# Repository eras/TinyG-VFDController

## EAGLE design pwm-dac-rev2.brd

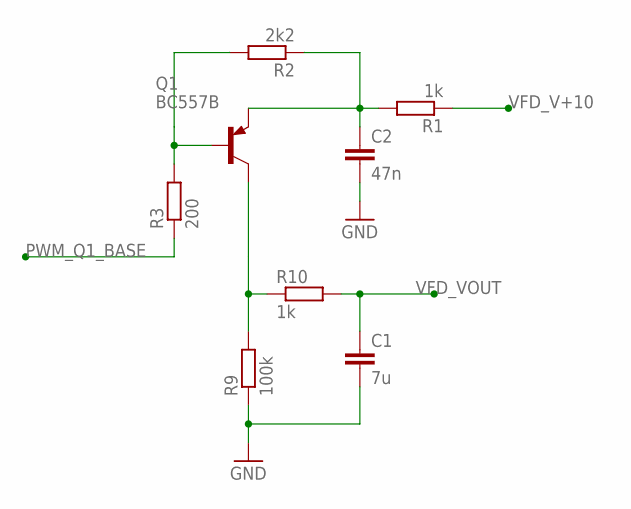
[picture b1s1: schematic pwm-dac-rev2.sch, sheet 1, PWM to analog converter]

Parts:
C1: 7u; C025-025X050
C2: 47n; C025-025X050
Q1: BC557B; TO92-EBC-OVAL
R1, R10: 1k; 0204/7
R2: 2k2; 0204/7
R3: 200; 0204/7
R9: 100k; 0204/7

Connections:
GND: C1.2, C2.2, R9.1; also elsewhere on the board
unnamed: C2.1, Q1.E, R1.2, R2.1
PWM_Q1_BASE: R3.1; also elsewhere on the board
Q3_B: Q1.B, R2.2, R3.2
Q3_C: Q1.C, R9.2, R10.1
VFD_V+10: R1.1; also elsewhere on the board
VFD_VOUT: C1.1, R10.2; also elsewhere on the board

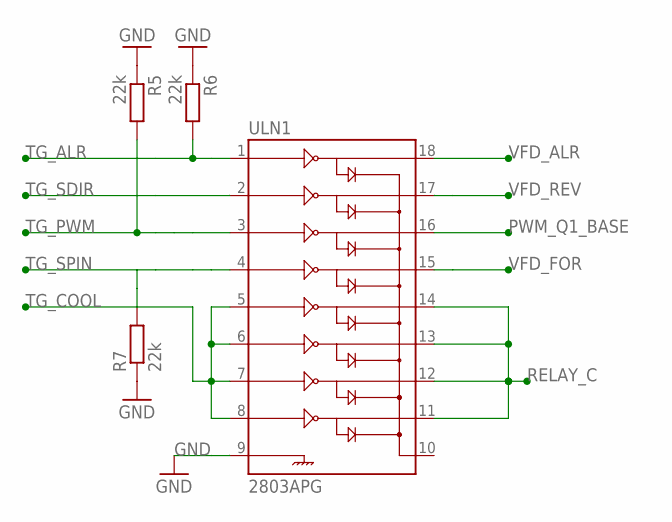
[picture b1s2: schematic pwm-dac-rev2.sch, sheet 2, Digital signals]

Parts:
R5, R6, R7: 22k; 0204/7
ULN1: 2803APG; DIL18

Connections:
GND: R5.1, R6.1, R7.1, ULN1.9; also elsewhere on the board
PWM_Q1_BASE: ULN1.16; also elsewhere on the board
RELAY_C: ULN1.11, ULN1.12, ULN1.13, ULN1.14; also elsewhere on the board
TG_ALR: R6.2, ULN1.1; also elsewhere on the board
TG_COOL: ULN1.5, ULN1.6, ULN1.7, ULN1.8; also elsewhere on the board
TG_PWM: R5.2, ULN1.3; also elsewhere on the board
TG_SDIR: ULN1.2; also elsewhere on the board
TG_SPIN: R7.2, ULN1.4; also elsewhere on the board
VFD_ALR: ULN1.18; also elsewhere on the board
VFD_FOR: ULN1.15; also elsewhere on the board
VFD_REV: ULN1.17; also elsewhere on the board

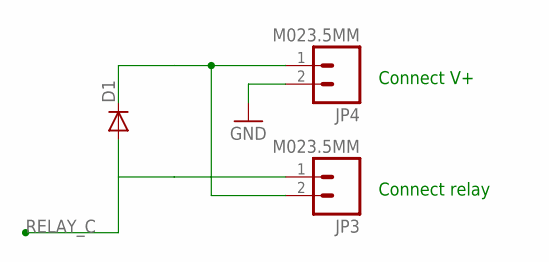
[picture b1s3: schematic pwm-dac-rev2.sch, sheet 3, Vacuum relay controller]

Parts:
D1: DIODE1N4148; DIODE-1N4148
JP3, JP4: M023.5MM; SCREWTERMINAL-3.5MM-2

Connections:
GND: JP4.2; also elsewhere on the board
unnamed: D1.C, JP3.2, JP4.1
RELAY_C: D1.A, JP3.1; also elsewhere on the board

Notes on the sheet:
Connect relay
Connect V+

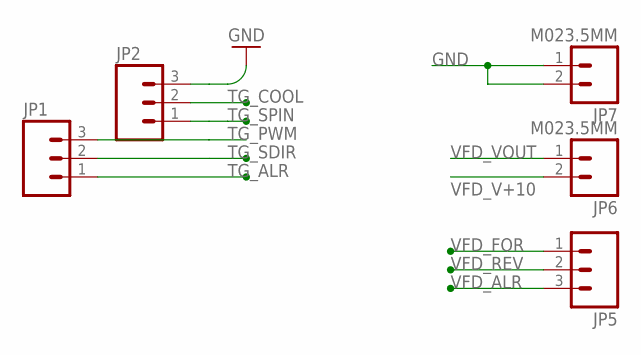
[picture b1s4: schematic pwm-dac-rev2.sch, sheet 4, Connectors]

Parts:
JP1, JP2, JP5: M03SCREW; SCREWTERMINAL-3.5MM-3
JP6, JP7: M023.5MM; SCREWTERMINAL-3.5MM-2

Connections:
GND: JP2.3, JP7.1, JP7.2; also elsewhere on the board
TG_ALR: JP1.1; also elsewhere on the board
TG_COOL: JP2.2; also elsewhere on the board
TG_PWM: JP1.3; also elsewhere on the board
TG_SDIR: JP1.2; also elsewhere on the board
TG_SPIN: JP2.1; also elsewhere on the board
VFD_ALR: JP5.3; also elsewhere on the board
VFD_FOR: JP5.1; also elsewhere on the board
VFD_REV: JP5.2; also elsewhere on the board
VFD_V+10: JP6.2; also elsewhere on the board
VFD_VOUT: JP6.1; also elsewhere on the board

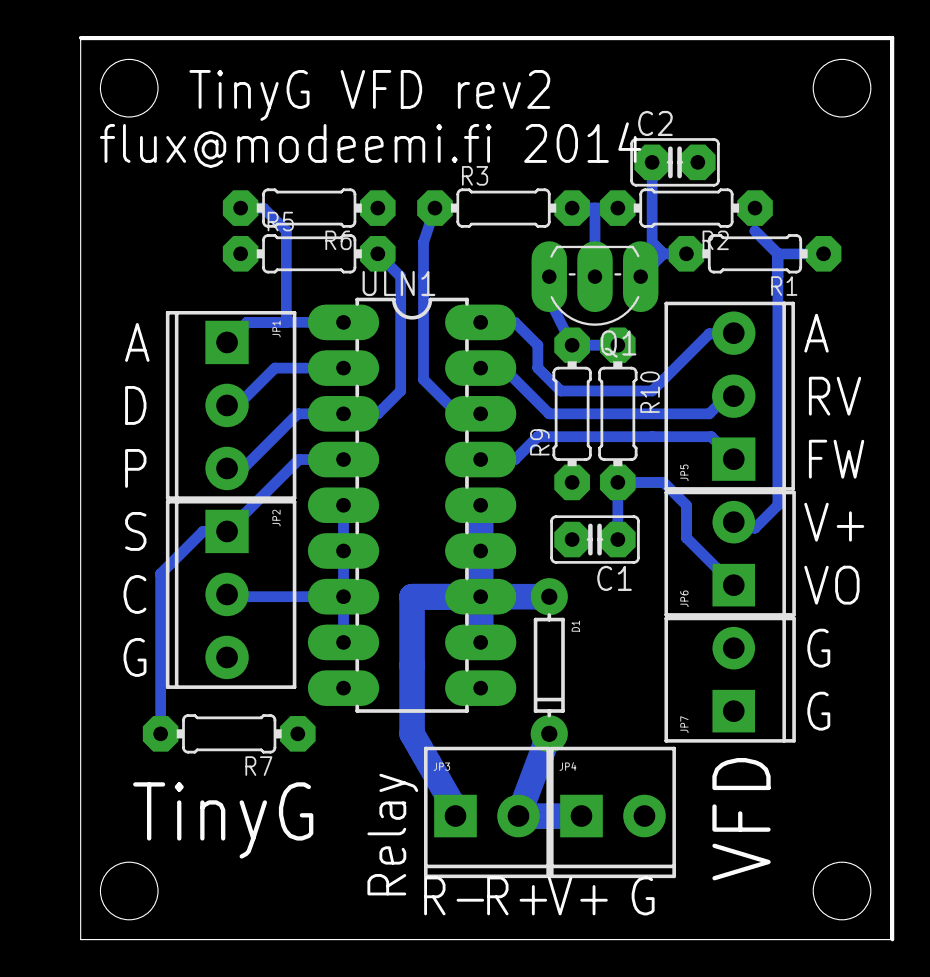
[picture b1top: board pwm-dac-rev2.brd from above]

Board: 2 copper layers, 45.0 x 50.0 mm, 20 parts (0 on the bottom side), 17 nets.

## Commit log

2014-07-21 PWM dac
2014-07-21 LICENSE.txt: added

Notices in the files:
parts and their libraries:
SparkFun: Licensing: CC v3.0 Share-Alike You are welcome to use this library for commercial purposes.
